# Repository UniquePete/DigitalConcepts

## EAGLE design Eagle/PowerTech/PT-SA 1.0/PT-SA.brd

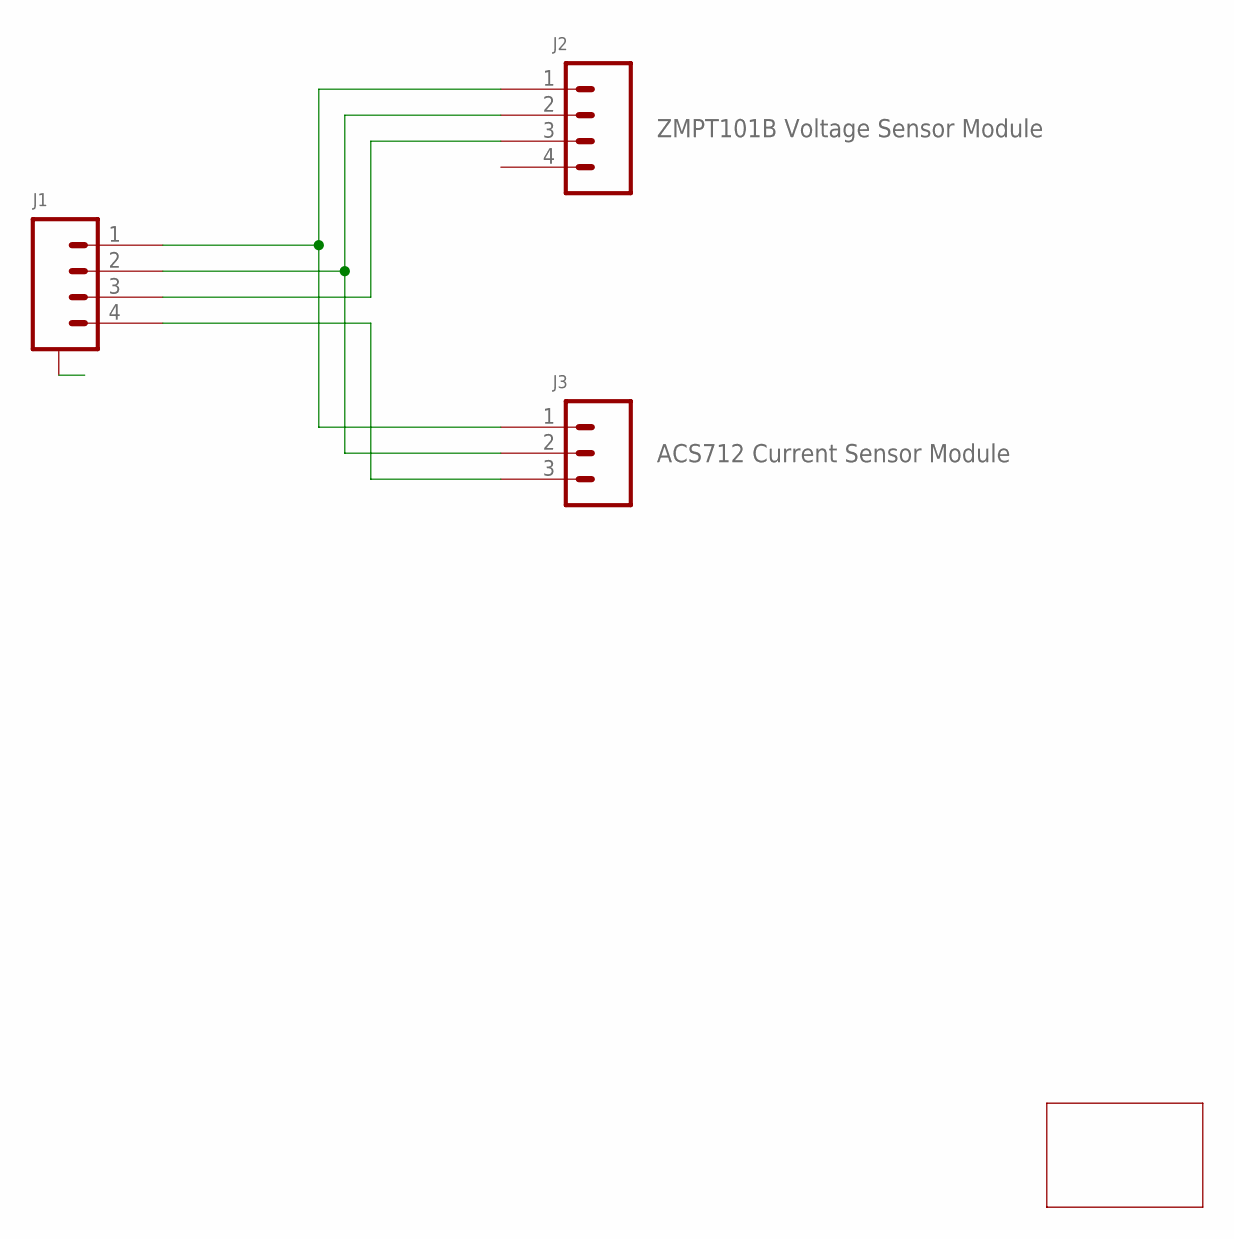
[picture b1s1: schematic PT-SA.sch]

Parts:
J1: JST-SH1.0-4-SMD-HORIZONTAL; JST-SH1.0-4-HORIZONTAL
J2: ZMPT101B Voltage Sensor Module; CONN_04-GENERIC
J3: ACS712 Current Sensor Module; CONN_03-GENERIC
PCB1: POWERTECH-SOCKET; PCB-POWERTECH

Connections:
A: J1.A@1 (A), J1.A@4 (A)
unnamed: J1.1, J2.1, J3.1
unnamed: J1.2, J2.2, J3.2
unnamed: J1.3, J2.3
unnamed: J1.4, J3.3

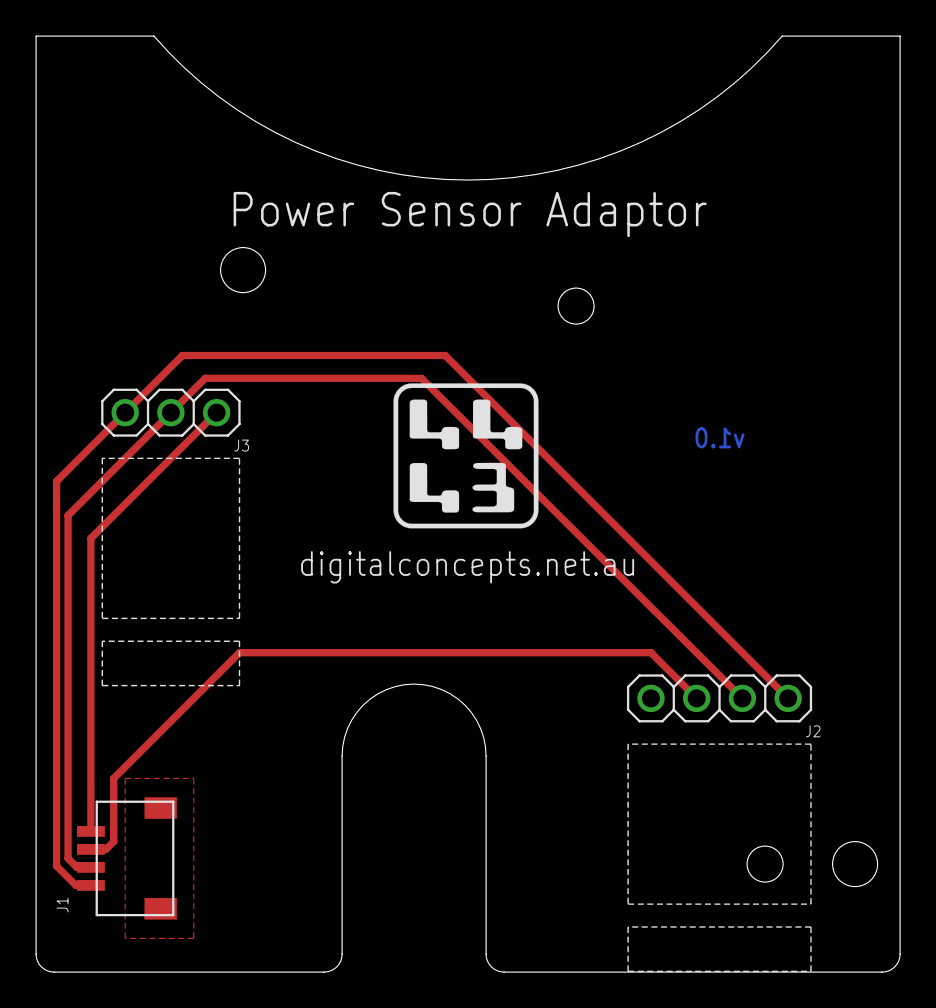
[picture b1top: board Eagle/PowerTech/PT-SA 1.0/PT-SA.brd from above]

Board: 2 copper layers, 48.0 x 52.0 mm, 4 parts (0 on the bottom side), 5 nets.

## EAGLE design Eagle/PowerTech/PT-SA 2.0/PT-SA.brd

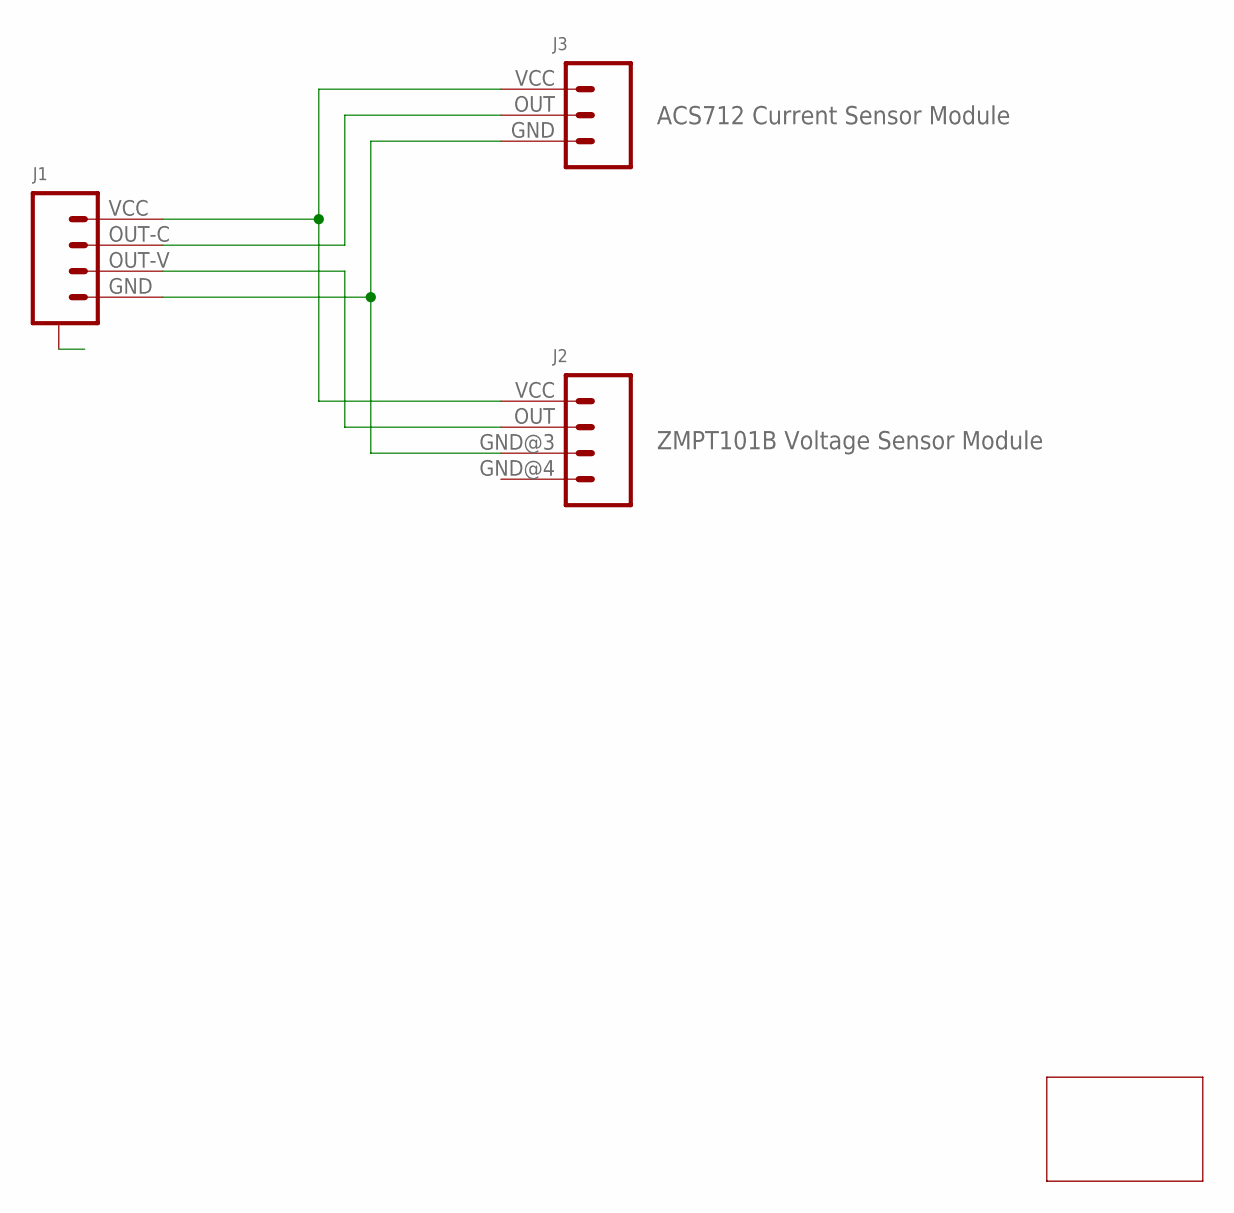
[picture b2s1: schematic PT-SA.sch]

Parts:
J1: JST-SH1.0-4-SMD-HORIZONTAL-POWERTECH; JST-SH1.0-4-HORIZONTAL-POWERTECH
J2: ZMPT101B Voltage Sensor Module; CONN_04-ZMPT101B
J3: ACS712 Current Sensor Module; CONN_03-ACS712
PCB1: POWERTECH-SOCKET; PCB-POWERTECH

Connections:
A: J1.A@1 (A), J1.A@4 (A)
unnamed: J1.VCC (1), J2.VCC (1), J3.VCC (1)
unnamed: J1.OUT-C (2), J3.OUT (2)
unnamed: J1.OUT-V (3), J2.OUT (2)
unnamed: J1.GND (4), J2.GND@3 (3), J3.GND (3)

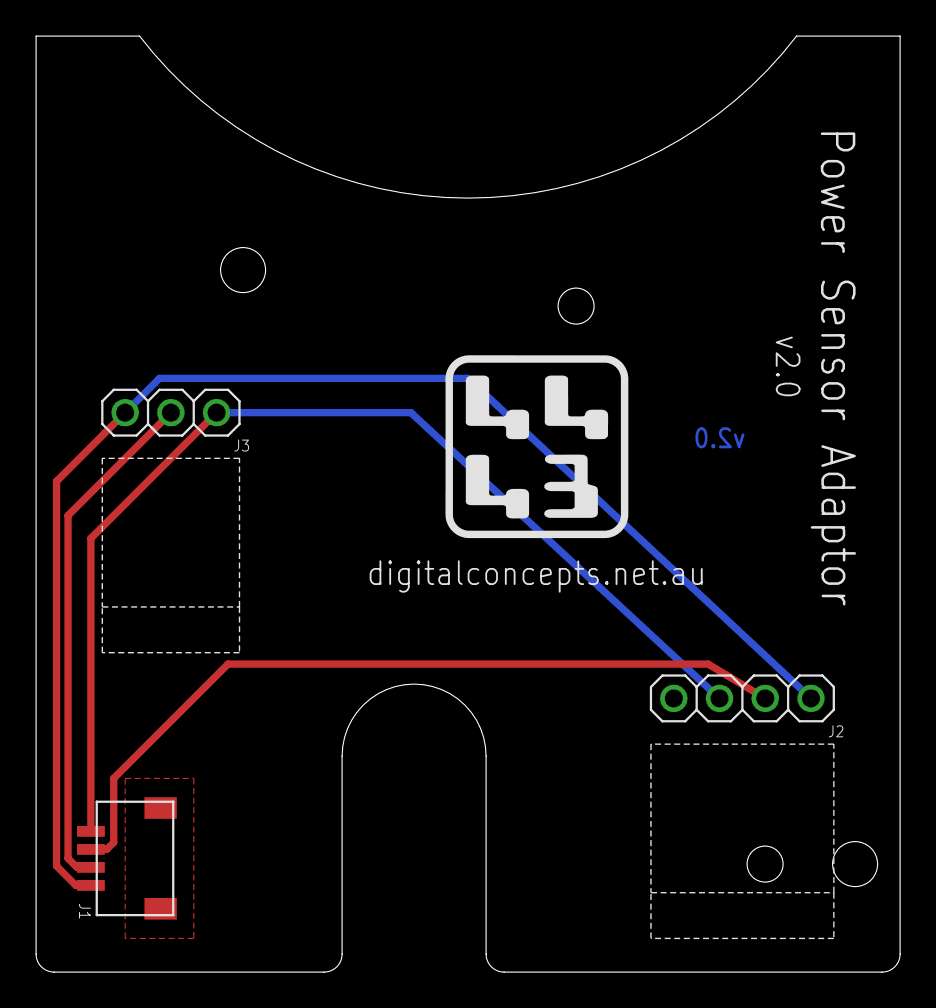
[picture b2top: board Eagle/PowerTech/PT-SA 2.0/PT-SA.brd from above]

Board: 2 copper layers, 48.0 x 52.0 mm, 4 parts (0 on the bottom side), 5 nets.

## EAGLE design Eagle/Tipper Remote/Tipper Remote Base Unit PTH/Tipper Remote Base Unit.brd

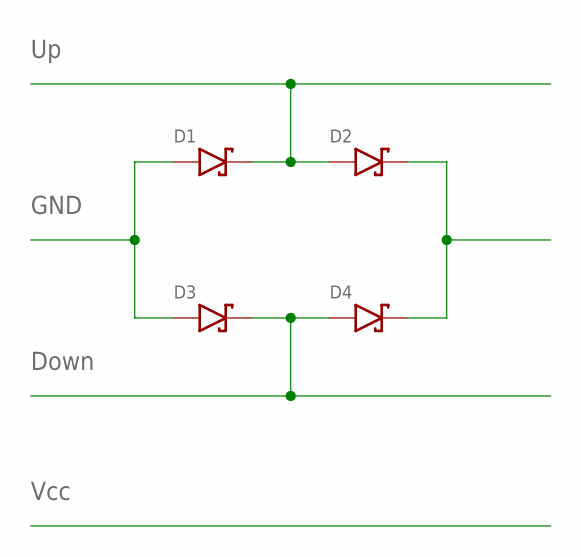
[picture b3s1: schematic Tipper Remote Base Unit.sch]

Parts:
D1, D2, D3, D4: DIODE-SCHOTTKY-20SQ045; DIODE_R-6

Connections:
unnamed: D1.C, D2.A
unnamed: D3.C, D4.A
unnamed: D1.A, D3.A
unnamed: D2.C, D4.C

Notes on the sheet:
Down
GND
Vcc

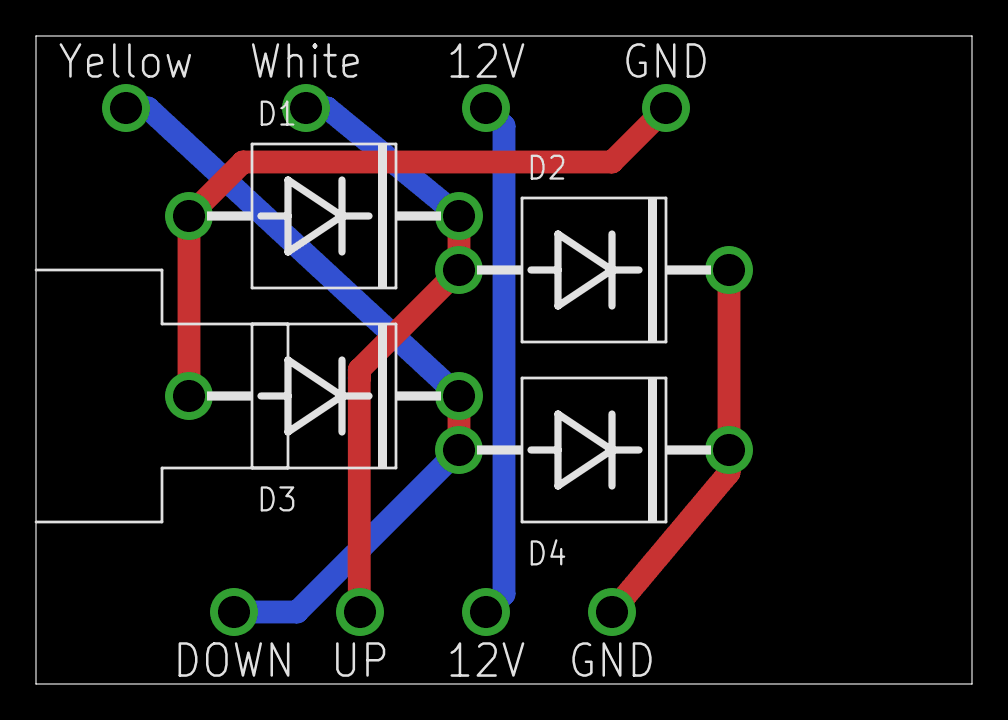
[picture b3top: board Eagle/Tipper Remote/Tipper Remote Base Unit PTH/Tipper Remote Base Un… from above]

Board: 2 copper layers, 52.0 x 36.0 mm, 4 parts (0 on the bottom side), 4 nets.

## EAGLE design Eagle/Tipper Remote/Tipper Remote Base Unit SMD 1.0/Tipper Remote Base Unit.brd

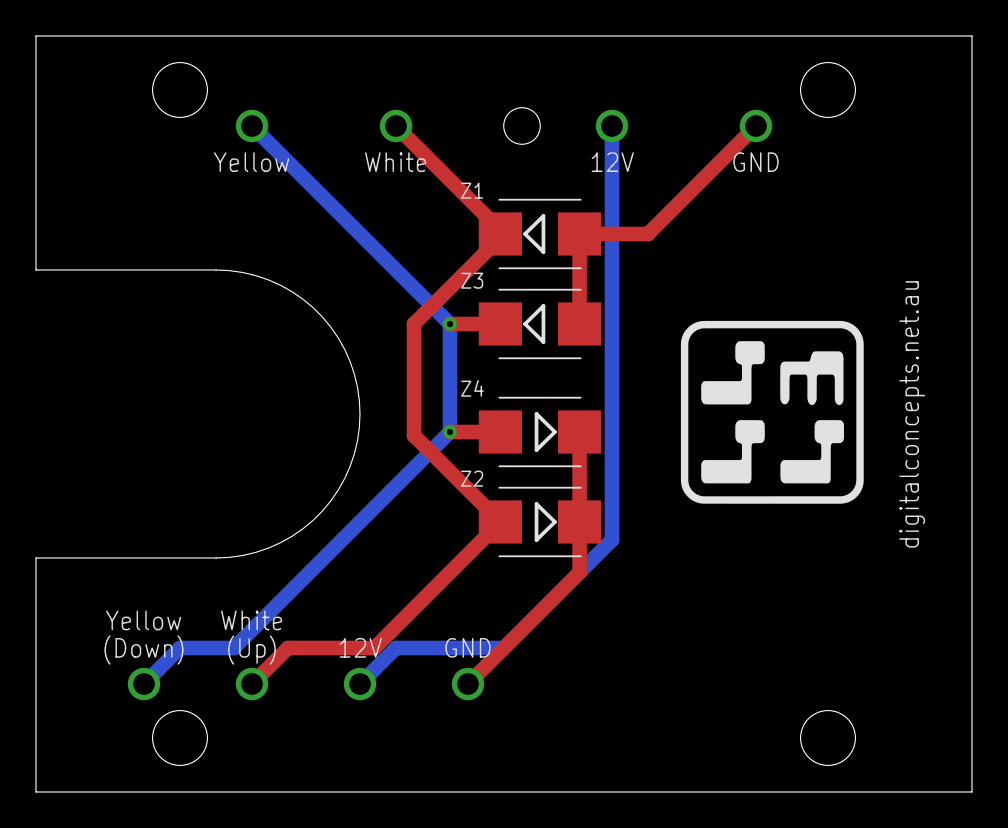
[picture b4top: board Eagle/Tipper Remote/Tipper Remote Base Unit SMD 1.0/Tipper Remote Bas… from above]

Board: 2 copper layers, 52.0 x 42.0 mm, 4 parts (0 on the bottom side), 4 nets.

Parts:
Z1, Z2, Z3, Z4: DIODE-SCHOTTKY-1N5822; DIODE_SMB

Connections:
unnamed: Z1.C, Z2.A
unnamed: Z3.C, Z4.A
unnamed: Z1.A, Z3.A
unnamed: Z2.C, Z4.C
